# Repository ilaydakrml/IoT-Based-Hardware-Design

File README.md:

# Tinkering-Low-Power-IoT-Based-Compact-Soil-Humidity-Monitoring-Device
cant get more self explanatory than that name but i will try

There is multiple designs in this repo with different design choices so as a starter,

## Simple humidity detector

  Basicly we use L7805 to voltage regulator to get a constant 5V voltage. Out pin of regulator is first connected to our resistive probe then base of BC547 transistor again we paraler connect the same  Out pin of regulator to a LED and from there the collector pin of the same BC547 resistor.
  The idea here is, if current wouldn't flow throug our resistive probe; our led won't light up. which would indicate our probe is embedded in dry soil, acourding to a resistive treshold.
  We also added a 50k potentiometer between base of our transistor and ground as a way to control this threshold.

## Low Power IoT Based Compact Soil Humidity Monitoring Device

In this second design, our planning will be to achieve the following things:
 - Having Soil sensor and the Microcontroller on a single board.
 - 18650 Lithium battery-based system
 - Reverse Polarity Protection for the battery
 - USB Port to program, get a log or charge the battery
 - Low power consumption
 - Wi-Fi Connectivity
 - Small size to be fit inside a 3D printed enclosure
 - A ready to use and ready to manufacturing cheap-ish product
 - Design the PCB
 - Ability to increase the Soil probe current.
 
  So in the first design we only designed a single functinality sensor module. In this second design we are much more interested in IoT and a Single device with multiple functionalities that have much more room to grow.

  i know its bit of a jump just bare with me i'll explain it. Also unfortunatly kicad's shematic to pdf converter doesnt work properly so this image is all you got for now.
  For better understanding, each section of the schematic is separated as a block as per the working principle of each major component.
  
  ### Aplication Center
  
  Ic in here is the ESP-12 microcontroller. Which is programmed by the programmer. It is a widely popular, low-cost, WiFi-based microcontroller that has more than enough pins for our design. 
The R6 is a 0R Jumper used to activate the deep sleep mode. It has 4 resistors for the pull-up in the IO0, IO2, EN, and RST Pins. The C1 and R4 are used to make a time delay circuit for proper reset in each reset state or each Power ON mode. It also has a pull-down resistor in the IO15. The Soil probe is connected in the two pins, IO5 and IO4. 
TX and RX are connected further to the UART to USB bridge. The SW1 and SW2 are used for the RST and Boot mode. It has an ADC pin and is used to measure the changes in the Soil Probe depending on the changes of the Soil Moisture.

### The Sensor Probe
How the moisture sensor works is that once you turn it on your current will start flowing through  and then it will come to your current limiting resistor (which is 100 ohm). And then it will go to your probe.

Probe will be buried inside the soil  and when it is inside the soil based on the amount of moisture present in the soil the current will reach the second probe and reach to the  base pin of the transistor. so when it reaches to the transistor might fully open or partially open telling us how much moisture is present in the soil.
The probe used in this design: https://github.com/sparkfun/Soil_Moisture_Sensor

### USB to UART:
RX-TX needs to be converted to the USB port. This is required to program the module and also for getting the required LOG in the UART terminal during development time. For this, we used the widely popular CP2102 Module.

There is a Jumper that is used to disconnect the CP2102 and its circuitry from the Power rail to save battery when the Probe is used in the application and not for development purposes. However, irrespective of the RST, BOOT switches, an auto configurable logic using a transistor is set to program the board with an autoboot and reset feature.

### The USB Input Section:
This USB input section has proper ESD protection to save the device from ESD surges. The USB connector used here is 629105136821. This is the part number Wurth Elektronic Micro USB Port. An equivalent USB port can also be used here since the package is generic. An LED is used here to provide information about the availability of USB Power.

### Battery Charging Section:
An Analog device IC, LTC4054ES5-4.2#TRMPBF is used to charge the lithium battery. This is an 800mA, 4.2V battery charger. The resistor R9 is used to provide 800mA of charge current to the battery. An LED on the charge status pin indicates the charging status. During the Charging period, it will glow constantly. It will stop glowing when the battery charging is completed.

### Reverse Polarity Protection Section:
Another major part is reverse Polarity protection. For that, we have used a high-Power P-channel MOSFET to provide the no drop reverse polarity protection. This MOSFET which is the Q2 will only turn ON if the battery is connected properly. If the battery is inserted in the reverse direction, the Q2 will be turned off and disconnect the entire circuitry from the battery. Additionally, D2 is used to protect the reverse current flow into the charger, when the USB is not plugged in, the Battery leakage current will significantly decrease. The Drop voltage of this diode will obviously affect the charging characteristic, but since it will rarely be used due to high battery backup, it is OK to compensate for that.

### i will add more detailed information about pin connections and pcb fabrication in time

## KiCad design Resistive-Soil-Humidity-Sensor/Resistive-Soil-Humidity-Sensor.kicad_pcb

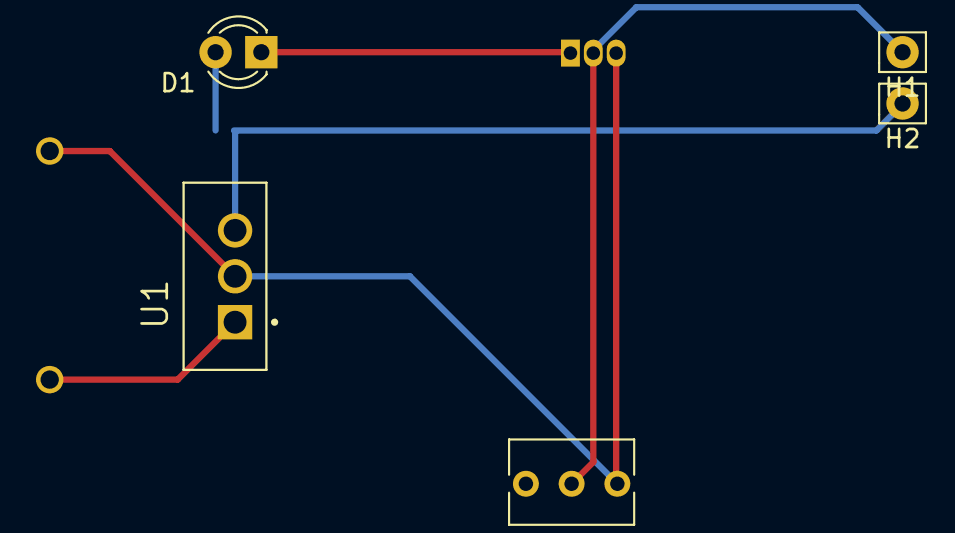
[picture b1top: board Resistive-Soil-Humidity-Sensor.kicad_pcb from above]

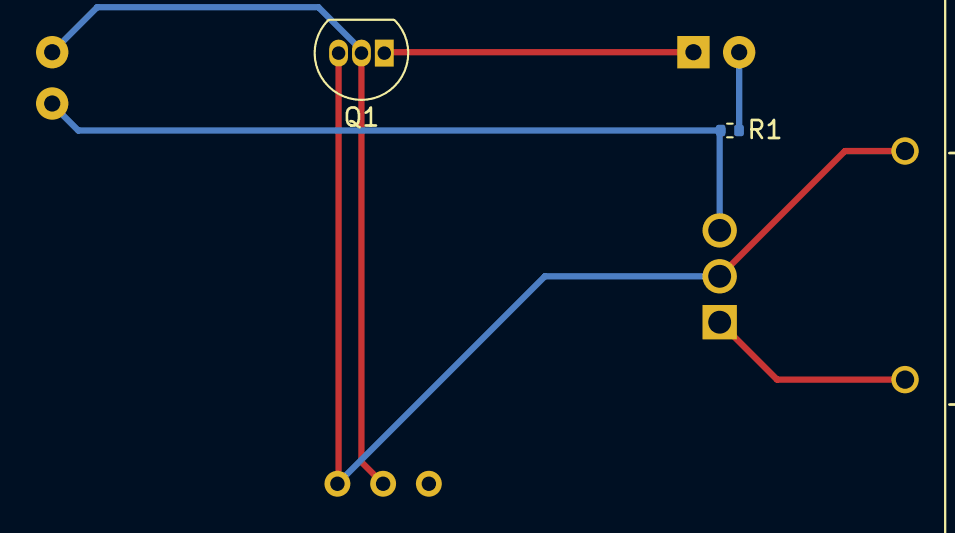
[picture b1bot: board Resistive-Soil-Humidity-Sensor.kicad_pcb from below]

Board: 2 copper layers, 8 parts (3 on the bottom side), 6 nets.

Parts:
9V1: BH9VPC; BAT_BH9VPC
D1: LED; LED_D3.0mm_FlatTop
H1, H2: MountingHole_Pad; Pin_D0.9mm_L10.0mm_W2.4mm_FlatFork
Q1: BC547; TO-92_Inline
R1: 1kohm; R_0402_1005Metric
RV1: R_POT; Potentiometer_Bourns_3266Y_Vertical
U1: L7805CV; TO255P1040X460X1968-3

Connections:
unnamed: 9V1.+, U1.1 (INPUT)
unnamed: 9V1.-, Q1.3 (E), RV1.3, U1.2 (GROUND)
unnamed: H2.1, R1.1, U1.3 (OUTPUT)
unnamed: D1.1 (K), Q1.1 (C)
unnamed: D1.2 (A), R1.2
unnamed: H1.1, Q1.2 (B), RV1.2

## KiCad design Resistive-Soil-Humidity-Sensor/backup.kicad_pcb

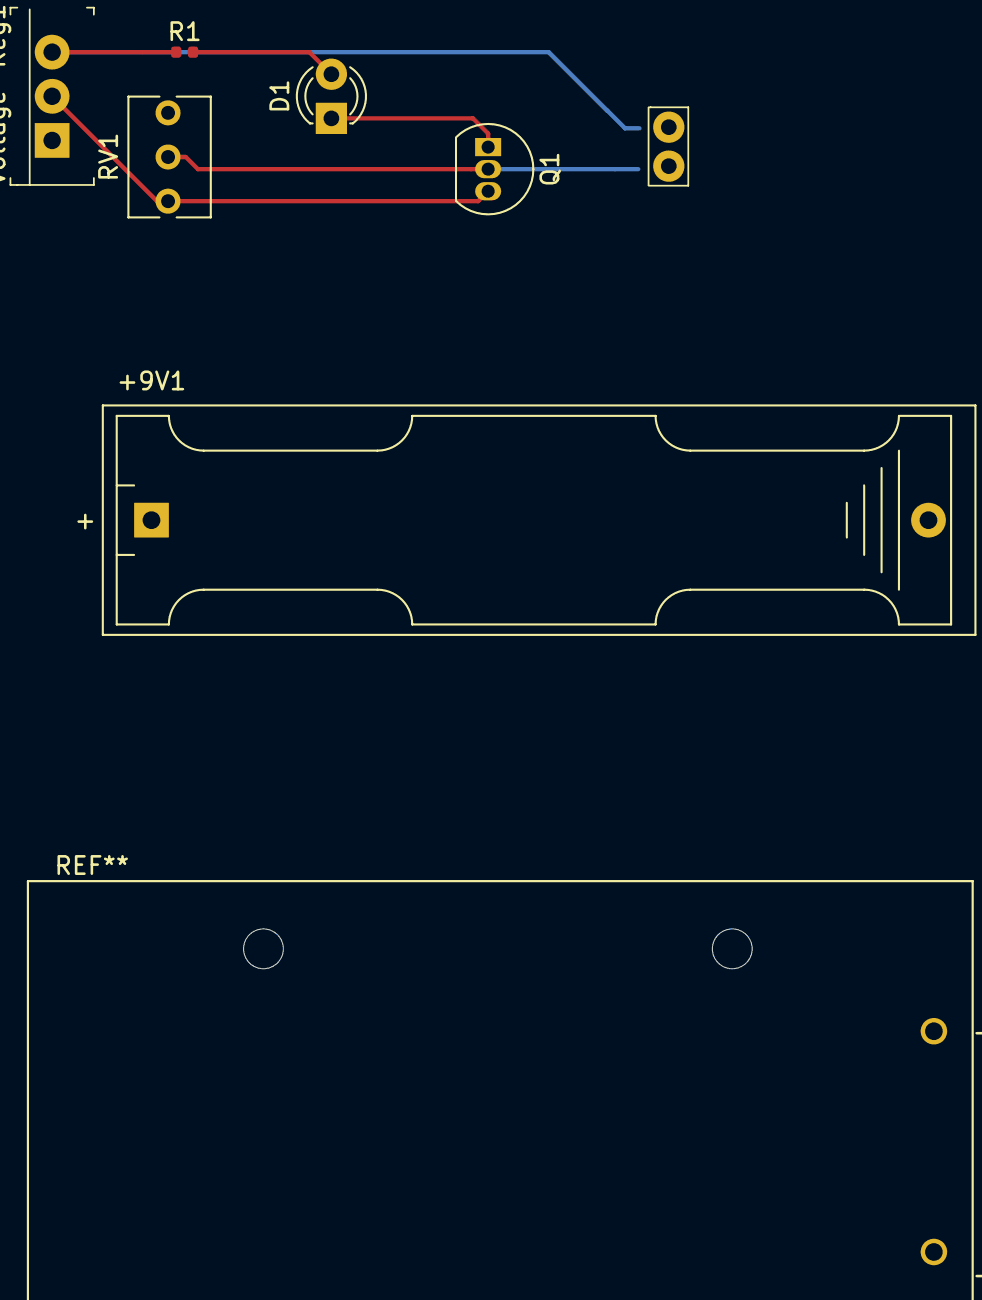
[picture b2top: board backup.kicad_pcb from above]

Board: 2 copper layers, 8 parts (0 on the bottom side), 6 nets.

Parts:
+9V1: Battery; BatteryHolder_Keystone_2466_1xAAA
D1: LED; LED_D3.0mm_FlatTop
H1, H2: MountingHole; MountingHole.1.8mm
Q1: BC547; TO-92_Inline
R1: 1kohm; R_0402_1005Metric
RV1: R_POT; Potentiometer_Bourns_3266Y_Vertical
Voltage-Reg1: L7805CV; TO-220-3

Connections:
unnamed: +9V1.1, Voltage-Reg1.1
unnamed: +9V1.2, Q1.3, RV1.3, Voltage-Reg1.2
unnamed: R1.1, Voltage-Reg1.3
unnamed: D1.1, Q1.1
unnamed: D1.2, R1.2
unnamed: Q1.2, RV1.2

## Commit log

2023-03-04 project from last year
